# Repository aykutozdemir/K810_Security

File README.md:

# K810_Security

## PlatformIO Build Instructions

### Prerequisites
- Python and pip installed
- PlatformIO installed (`pip install platformio`)

### Compilation
To compile the project, use one of these commands:
```bash
pio run
# or
platformio run
```

### Additional Useful Commands
- `pio run -t upload` - Compile and upload to the board
- `pio run -t clean` - Clean the build directory
- `pio run -t program` - Compile and program the board
- `pio device monitor` - Open the serial monitor

The compiled firmware will be placed in the `.pio/build/promicro16/` directory.

## Build Scripts

The project includes several Python scripts that enhance the build process:

### generate_version.py
Automatically increments and manages build version numbers. The version is stored in `version.txt` and is included in the firmware as a build flag.

### asembly_analyzer.py
Analyzes the assembly code of the compiled firmware, providing:
- Disassembly of the firmware
- Analysis of Interrupt Service Routines (ISRs)
- Register usage statistics
- Stack push/pop balance checking

Usage:
```bash
pio run -t disasm  # Generate and analyze disassembly
```

### map_analyzer.py
Analyzes the memory map of the compiled firmware, showing:
- Symbol sizes and addresses
- Memory usage by function
- Type of memory (code, data, BSS)

Usage:
```bash
python map_analyzer.py [--file path/to/firmware.elf] [--filter tTbBdD]
```

### custom_build.py
Applies custom build flags and optimizations:
- Disables unused parameter warnings
- Applies C++ specific optimizations
- Configures build environment for Arduino framework

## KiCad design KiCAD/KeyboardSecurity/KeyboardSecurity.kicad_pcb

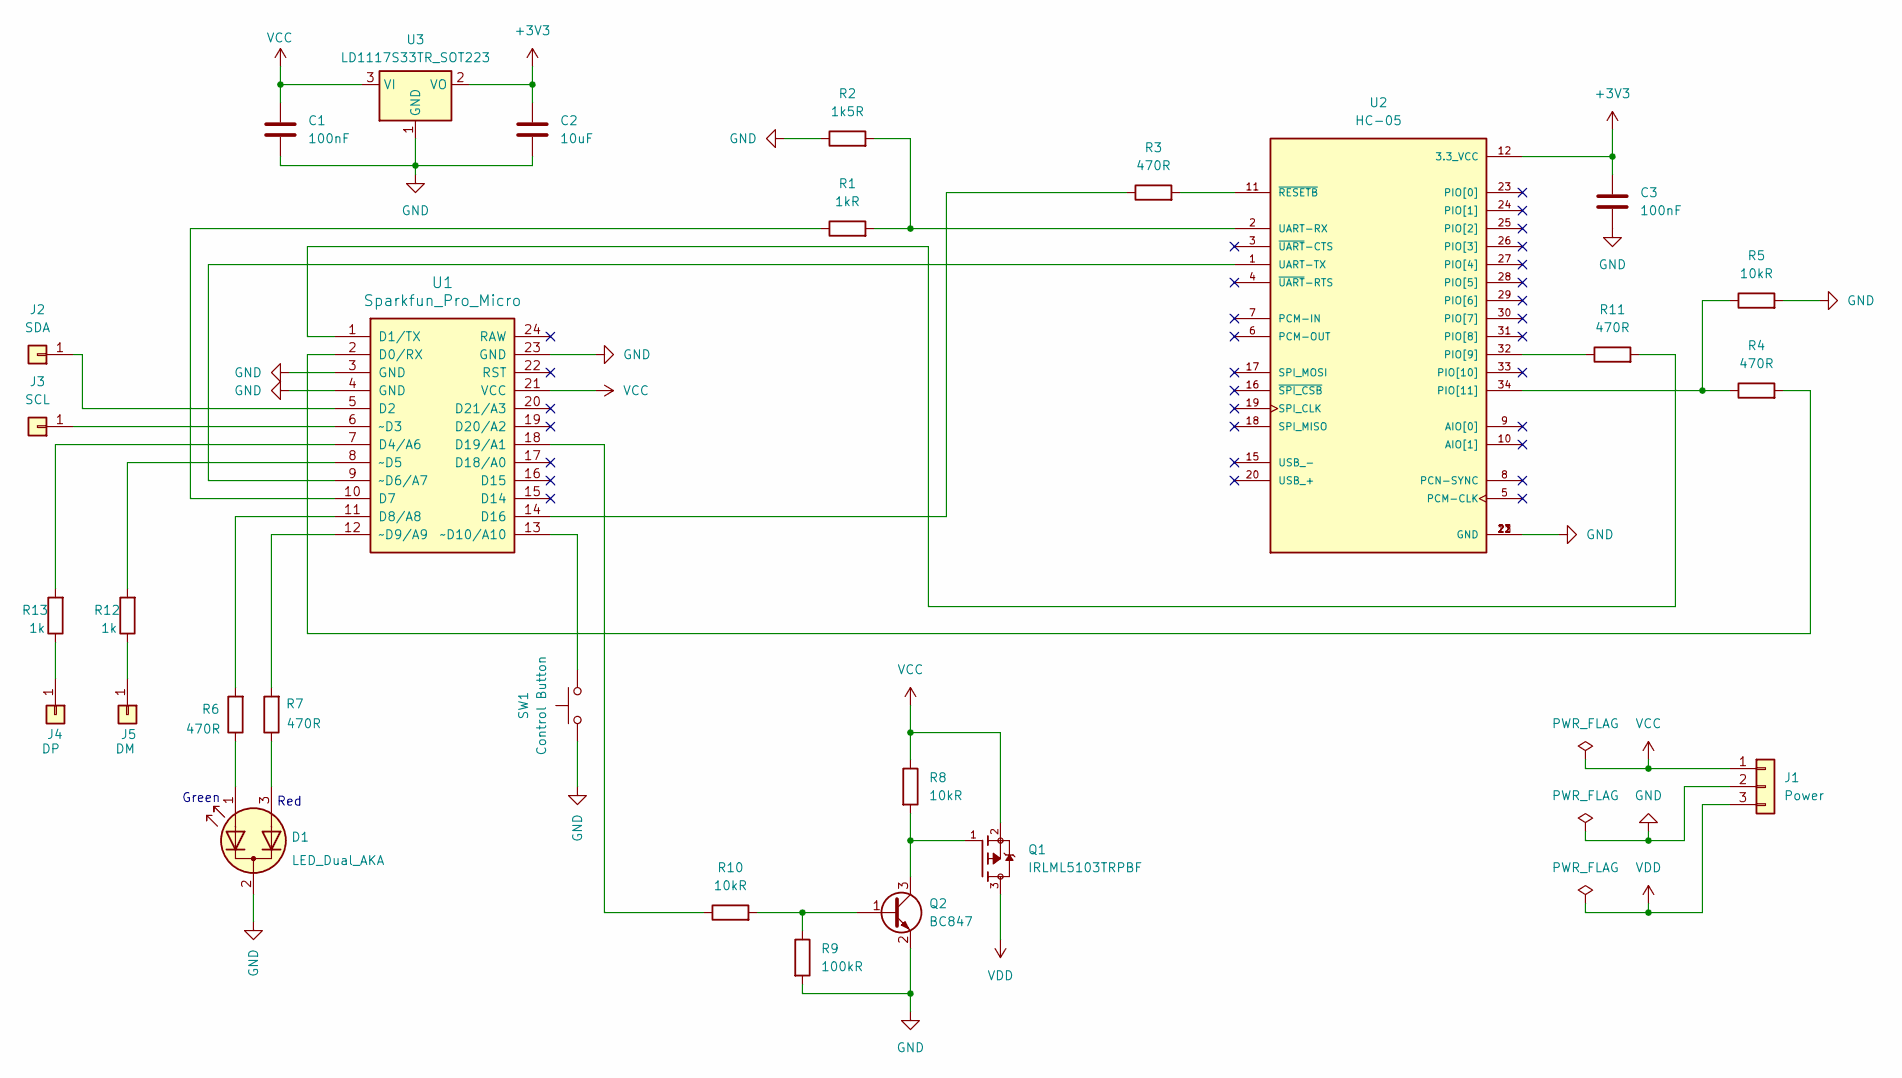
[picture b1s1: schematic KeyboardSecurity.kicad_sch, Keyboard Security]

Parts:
C1, C3: 100nF; C_0805_2012Metric
C2: 10uF; C_1812_4532Metric
D1: LED_Dual_AKA; PinHeader_1x03_P2.54mm_Vertical
J1: Power; PinHeader_1x03_P2.54mm_Vertical
J2: SDA; PinHeader_1x01_P2.54mm_Vertical
J3: SCL; PinHeader_1x01_P2.54mm_Vertical
J4: DP; PinHeader_1x01_P2.54mm_Vertical
J5: DM; PinHeader_1x01_P2.54mm_Vertical
Q1: IRLML5103TRPBF; SOT95P237X112-3N; PARTREV 4/24/2014
Q2: BC847; SOT-23
R1: 1kR; R_0805_2012Metric
R2: 1k5R; R_0805_2012Metric
R3, R4, R6, R7, R11: 470R; R_0805_2012Metric
R5, R8, R10: 10kR; R_0805_2012Metric
R9: 100kR; R_0805_2012Metric
R12, R13: 1k; R_0805_2012Metric
SW1: Control Button; PinHeader_1x02_P2.54mm_Vertical
U1: Sparkfun_Pro_Micro
U2: HC-05; XCVR_HC-05; PARTREV v1.0
U3: LD1117S33TR_SOT223; SOT-223-3_TabPin2

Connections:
+3V3: C2.1, C3.1, U2.12 (3.3_VCC), U3.2 (VO)
GND: C1.2, C2.2, C3.2, D1.2 (K), J1.2, Q2.2 (E), R2.1, R5.2, R9.2, SW1.1, U1.3 (GND), U1.4 (GND), U1.23 (GND), U2.13 (GND), U2.21 (GND), U2.22 (GND), U3.1 (GND)
unnamed: D1.1 (A1), R6.1
unnamed: D1.3 (A2), R7.1
unnamed: J2.1, U1.5 (D2)
unnamed: J3.1, U1.6 (~D3)
unnamed: J4.1, R13.1
unnamed: J5.1, R12.1
unnamed: Q2.1 (B), R9.1, R10.2
unnamed: Q1.1, Q2.3 (C), R8.2
unnamed: R4.2, U1.2 (D0/RX)
unnamed: R11.2, U1.1 (D1/TX)
unnamed: R13.2, U1.7 (D4/A6)
unnamed: R1.1, U1.10 (D7)
unnamed: R6.2, U1.11 (D8/A8)
unnamed: R3.1, U1.14 (D16)
unnamed: R10.1, U1.18 (D19/A1)
unnamed: R12.2, U1.8 (~D5)
unnamed: U1.9 (~D6/A7), U2.1 (UART-TX)
unnamed: R7.2, U1.12 (~D9/A9)
unnamed: SW1.2, U1.13 (~D10/A10)
unnamed: R11.1, U2.32 (PIO[9])
unnamed: R4.1, R5.1, U2.34 (PIO[11])
unnamed: R1.2, R2.2, U2.2 (UART-RX)
unnamed: R3.2, U2.11 (~RESETB)
VCC: C1.1, J1.1, Q1.2, R8.1, U1.21 (VCC), U3.3 (VI)
VDD: J1.3, Q1.3

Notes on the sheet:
Red
Green

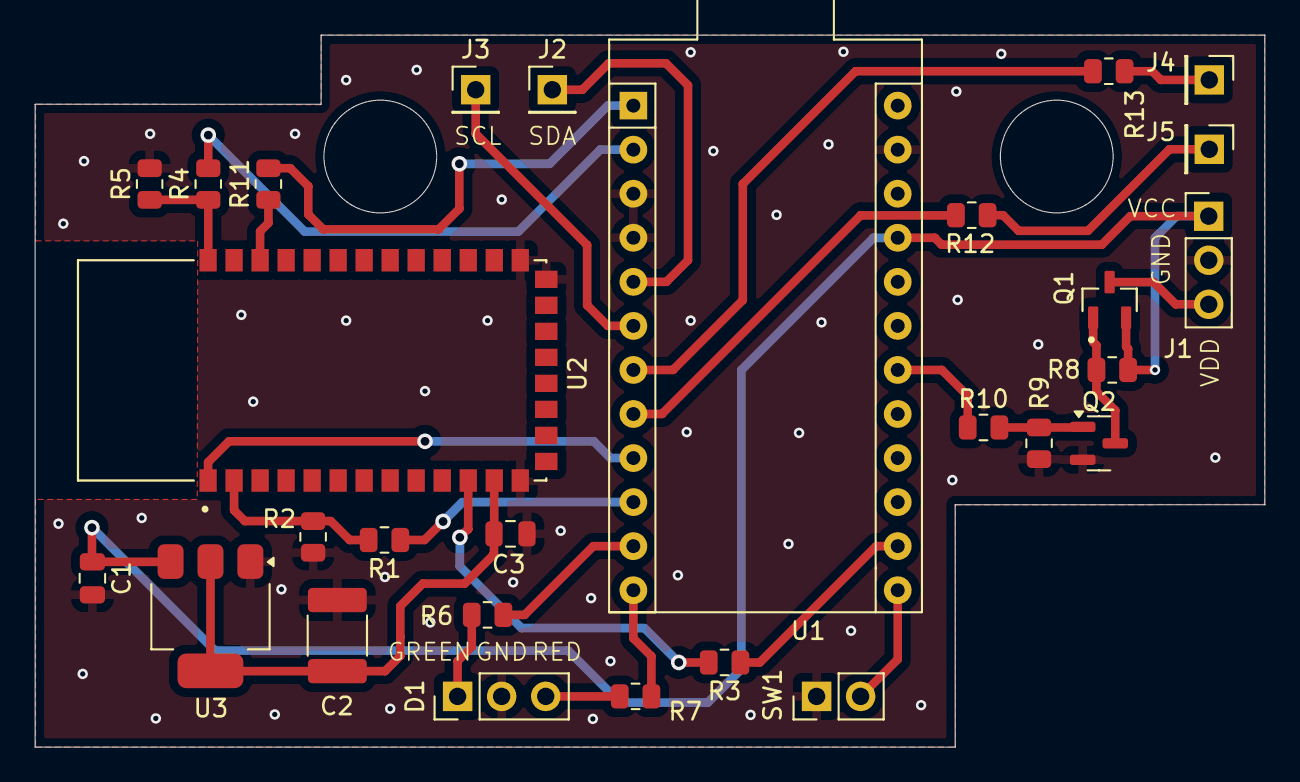
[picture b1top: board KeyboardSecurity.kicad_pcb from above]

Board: 2 copper layers, 70.9 x 41.0 mm, 28 parts (0 on the bottom side), 27 nets.

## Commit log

2025-02-15 Arduino K810 keypad security project
2025-02-15 Optimizations
2025-02-15 Formatting...
2025-02-17 Project moved to cursor platform io
2025-02-18 Optimizations applied
2025-02-18 Soft serial optimizations
2025-02-18 Soft serial fixes
2025-02-26 Reset reason implemented, wdt isr implemented, lots of improvements on soft serial and hc05 driver
2025-02-27 Doc formattings and bug fixes
2025-03-02 Package interface implemented for uart
2025-03-12 Lots of improvements, comments and bug fixes
2025-03-14 Soft serial fixed
2025-03-16 Crc packager interface completed.
2025-03-25 Trace library implemented
2025-03-27 Traceable class implemented, lots of improvement and size optimization
2025-03-29 Traceable commands implemented
2025-03-29 Formating fixes, new trace related commands
2025-04-01 Project completed
2025-04-01 Auto lock when bt gone
2025-04-01 Updated java version of packager
2025-05-26 Android project added
